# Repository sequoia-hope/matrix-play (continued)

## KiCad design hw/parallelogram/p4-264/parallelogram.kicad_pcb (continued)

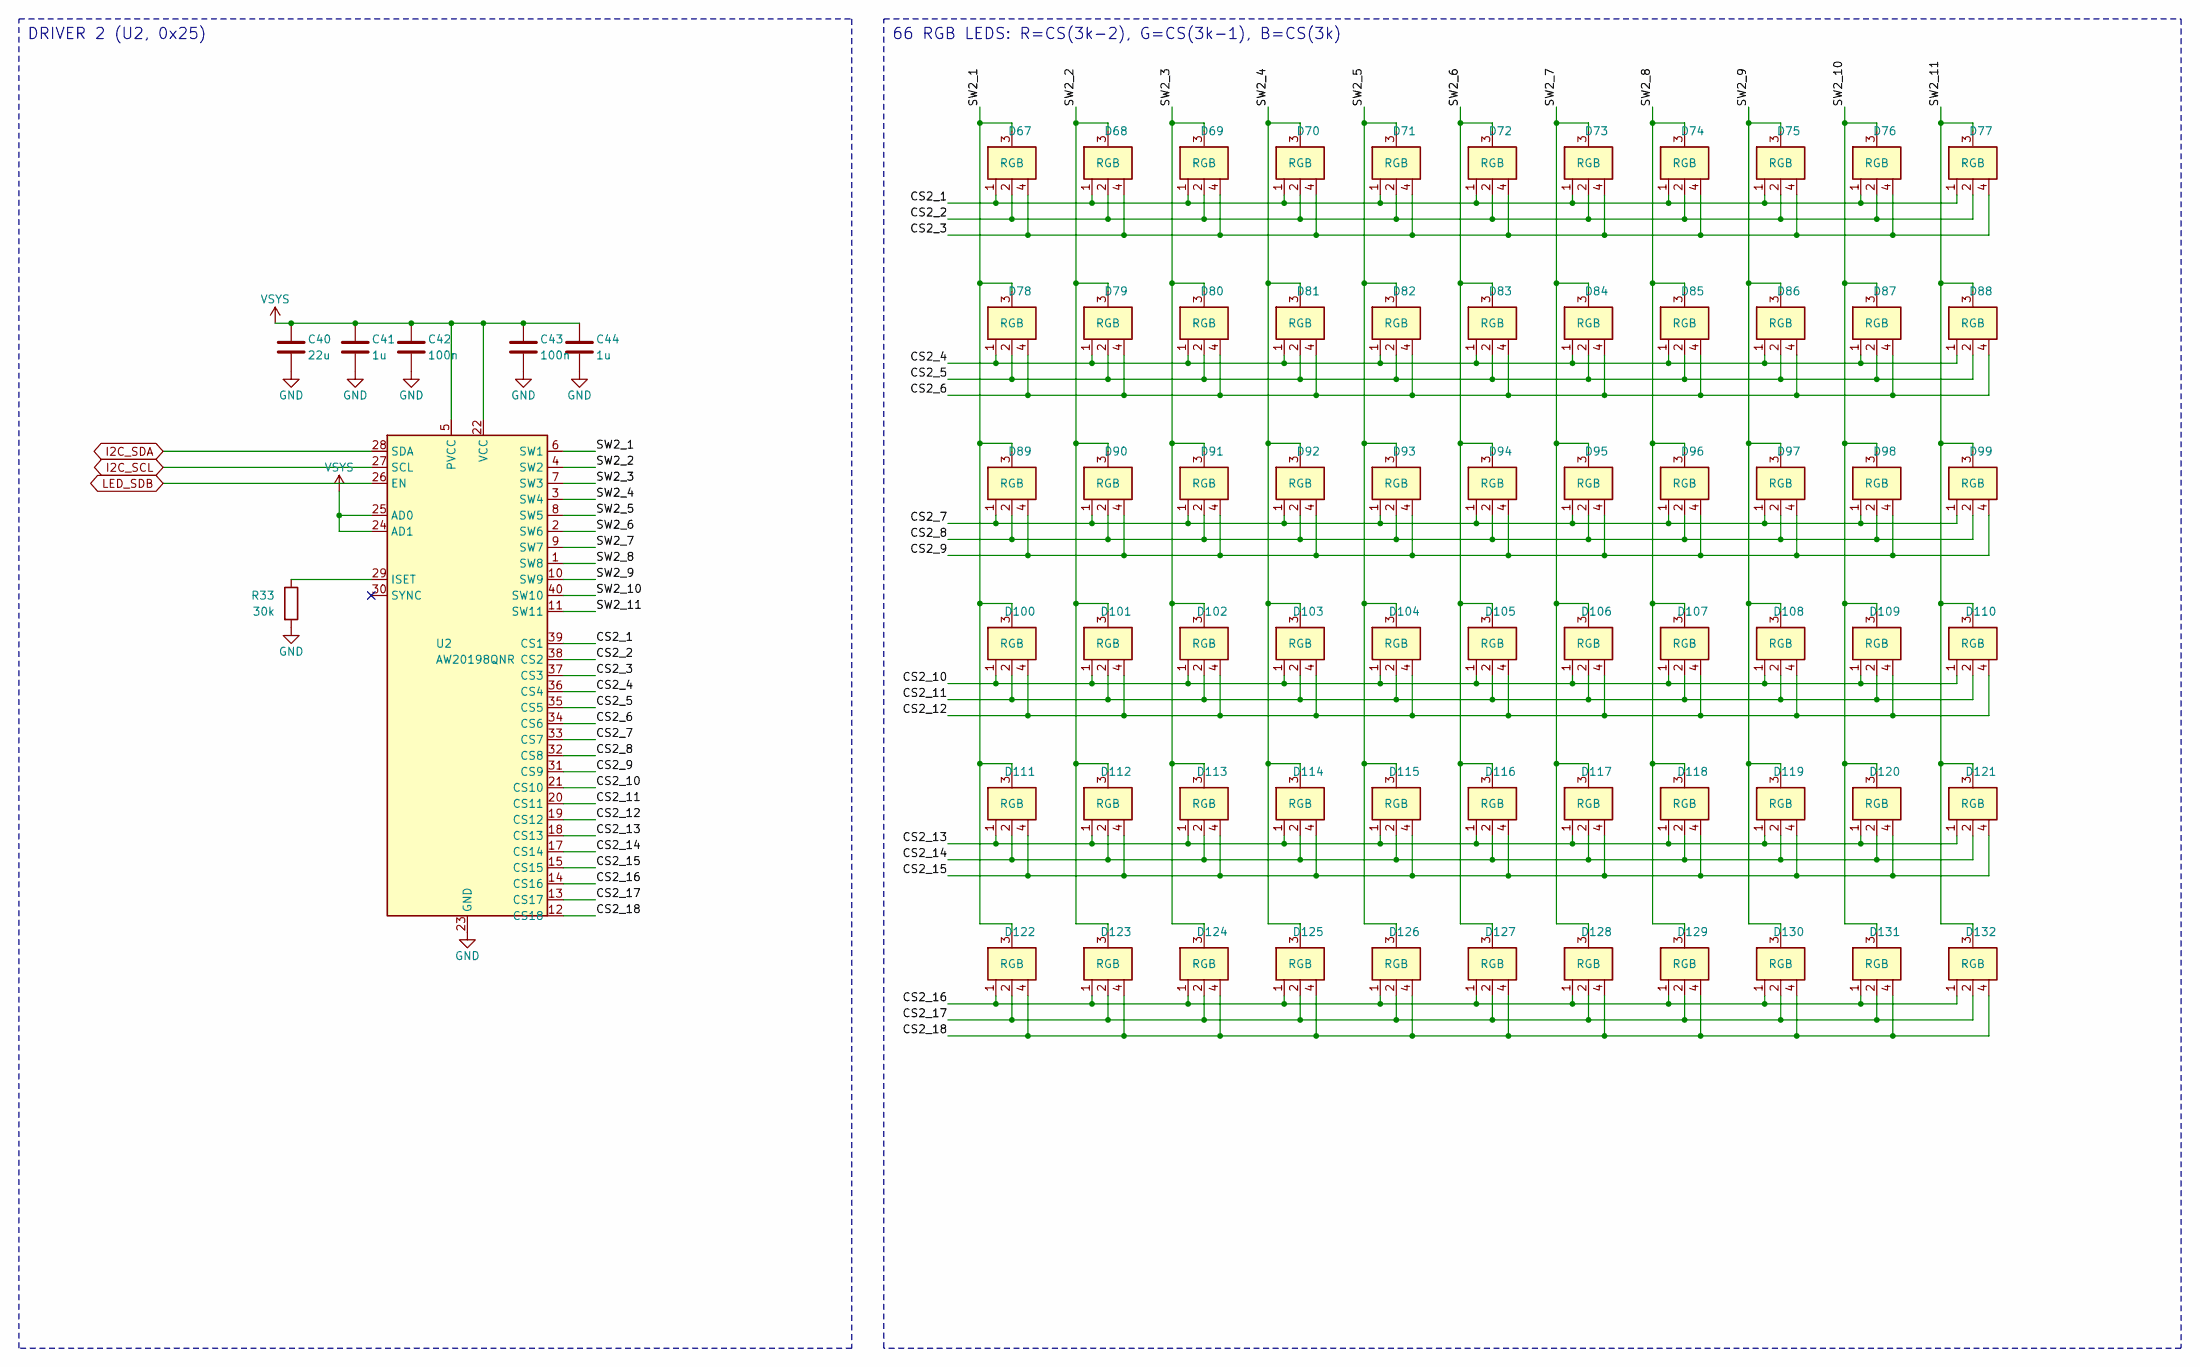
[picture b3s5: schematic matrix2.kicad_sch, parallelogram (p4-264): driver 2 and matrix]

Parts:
C40: 22u; C_0603_1608Metric; MPN CL10A226MP8NUNE; LCSC C86295
C41, C44: 1u; C_0402_1005Metric; MPN CL05A105KA5NQNC; LCSC C52923
C42, C43: 100n; C_0402_1005Metric; MPN CL05B104KO5NNNC; LCSC C1525
D67, D68, D69, D70, D71, D72, D73, D74, D75, D76, D77, D78, D79, D80, D81, D82, D83, D84, D85, D86, D87, D88, D89, D90, D91, D92, D93, D94, D95, D96, D97, D98, D99, D100, D101, D102, D103, D104, D105, D106, D107, D108, D109, D110, D111, D112, D113, D114, D115, D116, D117, D118, D119, D120, D121, D122, D123, D124, D125, D126, D127, D128, D129, D130, D131, D132: RGB; LED_XL-1010RGB; MPN XL-1010RGB-YG; LCSC C965834
R33: 30k; R_0402_1005Metric; MPN 0402WGF3002TCE; LCSC C25776
U2: AW20198QNR; AW20198_QFN-40-1EP_5x5mm_P0.4mm_EP3.4x3.4mm; MPN AW20198QNR; LCSC C5137654

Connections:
/Driver 2 and matrix/CS2_1: D67.1 (R), D68.1 (R), D69.1 (R), D70.1 (R), D71.1 (R), D72.1 (R), D73.1 (R), D74.1 (R), D75.1 (R), D76.1 (R), D77.1 (R), U2.39 (CS1)
/Driver 2 and matrix/CS2_2: D67.2 (G), D68.2 (G), D69.2 (G), D70.2 (G), D71.2 (G), D72.2 (G), D73.2 (G), D74.2 (G), D75.2 (G), D76.2 (G), D77.2 (G), U2.38 (CS2)
/Driver 2 and matrix/CS2_3: D67.4 (B), D68.4 (B), D69.4 (B), D70.4 (B), D71.4 (B), D72.4 (B), D73.4 (B), D74.4 (B), D75.4 (B), D76.4 (B), D77.4 (B), U2.37 (CS3)
/Driver 2 and matrix/CS2_4: D78.1 (R), D79.1 (R), D80.1 (R), D81.1 (R), D82.1 (R), D83.1 (R), D84.1 (R), D85.1 (R), D86.1 (R), D87.1 (R), D88.1 (R), U2.36 (CS4)
/Driver 2 and matrix/CS2_5: D78.2 (G), D79.2 (G), D80.2 (G), D81.2 (G), D82.2 (G), D83.2 (G), D84.2 (G), D85.2 (G), D86.2 (G), D87.2 (G), D88.2 (G), U2.35 (CS5)
/Driver 2 and matrix/CS2_6: D78.4 (B), D79.4 (B), D80.4 (B), D81.4 (B), D82.4 (B), D83.4 (B), D84.4 (B), D85.4 (B), D86.4 (B), D87.4 (B), D88.4 (B), U2.34 (CS6)
/Driver 2 and matrix/CS2_7: D89.1 (R), D90.1 (R), D91.1 (R), D92.1 (R), D93.1 (R), D94.1 (R), D95.1 (R), D96.1 (R), D97.1 (R), D98.1 (R), D99.1 (R), U2.33 (CS7)
/Driver 2 and matrix/CS2_8: D89.2 (G), D90.2 (G), D91.2 (G), D92.2 (G), D93.2 (G), D94.2 (G), D95.2 (G), D96.2 (G), D97.2 (G), D98.2 (G), D99.2 (G), U2.32 (CS8)
/Driver 2 and matrix/CS2_9: D89.4 (B), D90.4 (B), D91.4 (B), D92.4 (B), D93.4 (B), D94.4 (B), D95.4 (B), D96.4 (B), D97.4 (B), D98.4 (B), D99.4 (B), U2.31 (CS9)
/Driver 2 and matrix/CS2_10: D100.1 (R), D101.1 (R), D102.1 (R), D103.1 (R), D104.1 (R), D105.1 (R), D106.1 (R), D107.1 (R), D108.1 (R), D109.1 (R), D110.1 (R), U2.21 (CS10)
/Driver 2 and matrix/CS2_11: D100.2 (G), D101.2 (G), D102.2 (G), D103.2 (G), D104.2 (G), D105.2 (G), D106.2 (G), D107.2 (G), D108.2 (G), D109.2 (G), D110.2 (G), U2.20 (CS11)
/Driver 2 and matrix/CS2_12: D100.4 (B), D101.4 (B), D102.4 (B), D103.4 (B), D104.4 (B), D105.4 (B), D106.4 (B), D107.4 (B), D108.4 (B), D109.4 (B), D110.4 (B), U2.19 (CS12)
/Driver 2 and matrix/CS2_13: D111.1 (R), D112.1 (R), D113.1 (R), D114.1 (R), D115.1 (R), D116.1 (R), D117.1 (R), D118.1 (R), D119.1 (R), D120.1 (R), D121.1 (R), U2.18 (CS13)
/Driver 2 and matrix/CS2_14: D111.2 (G), D112.2 (G), D113.2 (G), D114.2 (G), D115.2 (G), D116.2 (G), D117.2 (G), D118.2 (G), D119.2 (G), D120.2 (G), D121.2 (G), U2.17 (CS14)
/Driver 2 and matrix/CS2_15: D111.4 (B), D112.4 (B), D113.4 (B), D114.4 (B), D115.4 (B), D116.4 (B), D117.4 (B), D118.4 (B), D119.4 (B), D120.4 (B), D121.4 (B), U2.15 (CS15)
/Driver 2 and matrix/CS2_16: D122.1 (R), D123.1 (R), D124.1 (R), D125.1 (R), D126.1 (R), D127.1 (R), D128.1 (R), D129.1 (R), D130.1 (R), D131.1 (R), D132.1 (R), U2.14 (CS16)
/Driver 2 and matrix/CS2_17: D122.2 (G), D123.2 (G), D124.2 (G), D125.2 (G), D126.2 (G), D127.2 (G), D128.2 (G), D129.2 (G), D130.2 (G), D131.2 (G), D132.2 (G), U2.13 (CS17)
/Driver 2 and matrix/CS2_18: D122.4 (B), D123.4 (B), D124.4 (B), D125.4 (B), D126.4 (B), D127.4 (B), D128.4 (B), D129.4 (B), D130.4 (B), D131.4 (B), D132.4 (B), U2.12 (CS18)
/Driver 2 and matrix/SW2_1: D67.3 (A), D78.3 (A), D89.3 (A), D100.3 (A), D111.3 (A), D122.3 (A), U2.6 (SW1)
/Driver 2 and matrix/SW2_2: D68.3 (A), D79.3 (A), D90.3 (A), D101.3 (A), D112.3 (A), D123.3 (A), U2.4 (SW2)
/Driver 2 and matrix/SW2_3: D69.3 (A), D80.3 (A), D91.3 (A), D102.3 (A), D113.3 (A), D124.3 (A), U2.7 (SW3)
/Driver 2 and matrix/SW2_4: D70.3 (A), D81.3 (A), D92.3 (A), D103.3 (A), D114.3 (A), D125.3 (A), U2.3 (SW4)
/Driver 2 and matrix/SW2_5: D71.3 (A), D82.3 (A), D93.3 (A), D104.3 (A), D115.3 (A), D126.3 (A), U2.8 (SW5)
/Driver 2 and matrix/SW2_6: D72.3 (A), D83.3 (A), D94.3 (A), D105.3 (A), D116.3 (A), D127.3 (A), U2.2 (SW6)
/Driver 2 and matrix/SW2_7: D73.3 (A), D84.3 (A), D95.3 (A), D106.3 (A), D117.3 (A), D128.3 (A), U2.9 (SW7)
/Driver 2 and matrix/SW2_8: D74.3 (A), D85.3 (A), D96.3 (A), D107.3 (A), D118.3 (A), D129.3 (A), U2.1 (SW8)
/Driver 2 and matrix/SW2_9: D75.3 (A), D86.3 (A), D97.3 (A), D108.3 (A), D119.3 (A), D130.3 (A), U2.10 (SW9)
/Driver 2 and matrix/SW2_10: D76.3 (A), D87.3 (A), D98.3 (A), D109.3 (A), D120.3 (A), D131.3 (A), U2.40 (SW10)
/Driver 2 and matrix/SW2_11: D77.3 (A), D88.3 (A), D99.3 (A), D110.3 (A), D121.3 (A), D132.3 (A), U2.11 (SW11)
I2C_SCL: U2.27 (SCL); also elsewhere on the board
I2C_SDA: U2.28 (SDA); also elsewhere on the board
LED_SDB: U2.26 (EN); also elsewhere on the board
unnamed: R33.1, U2.29 (ISET)
VSYS: C40.1, C41.1, C42.1, C43.1, C44.1, U2.5 (PVCC), U2.22 (VCC), U2.24 (AD1), U2.25 (AD0); also elsewhere on the board

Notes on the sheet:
DRIVER 2 (U2, 0x25)
66 RGB LEDS: R=CS(3k-2), G=CS(3k-1), B=CS(3k)

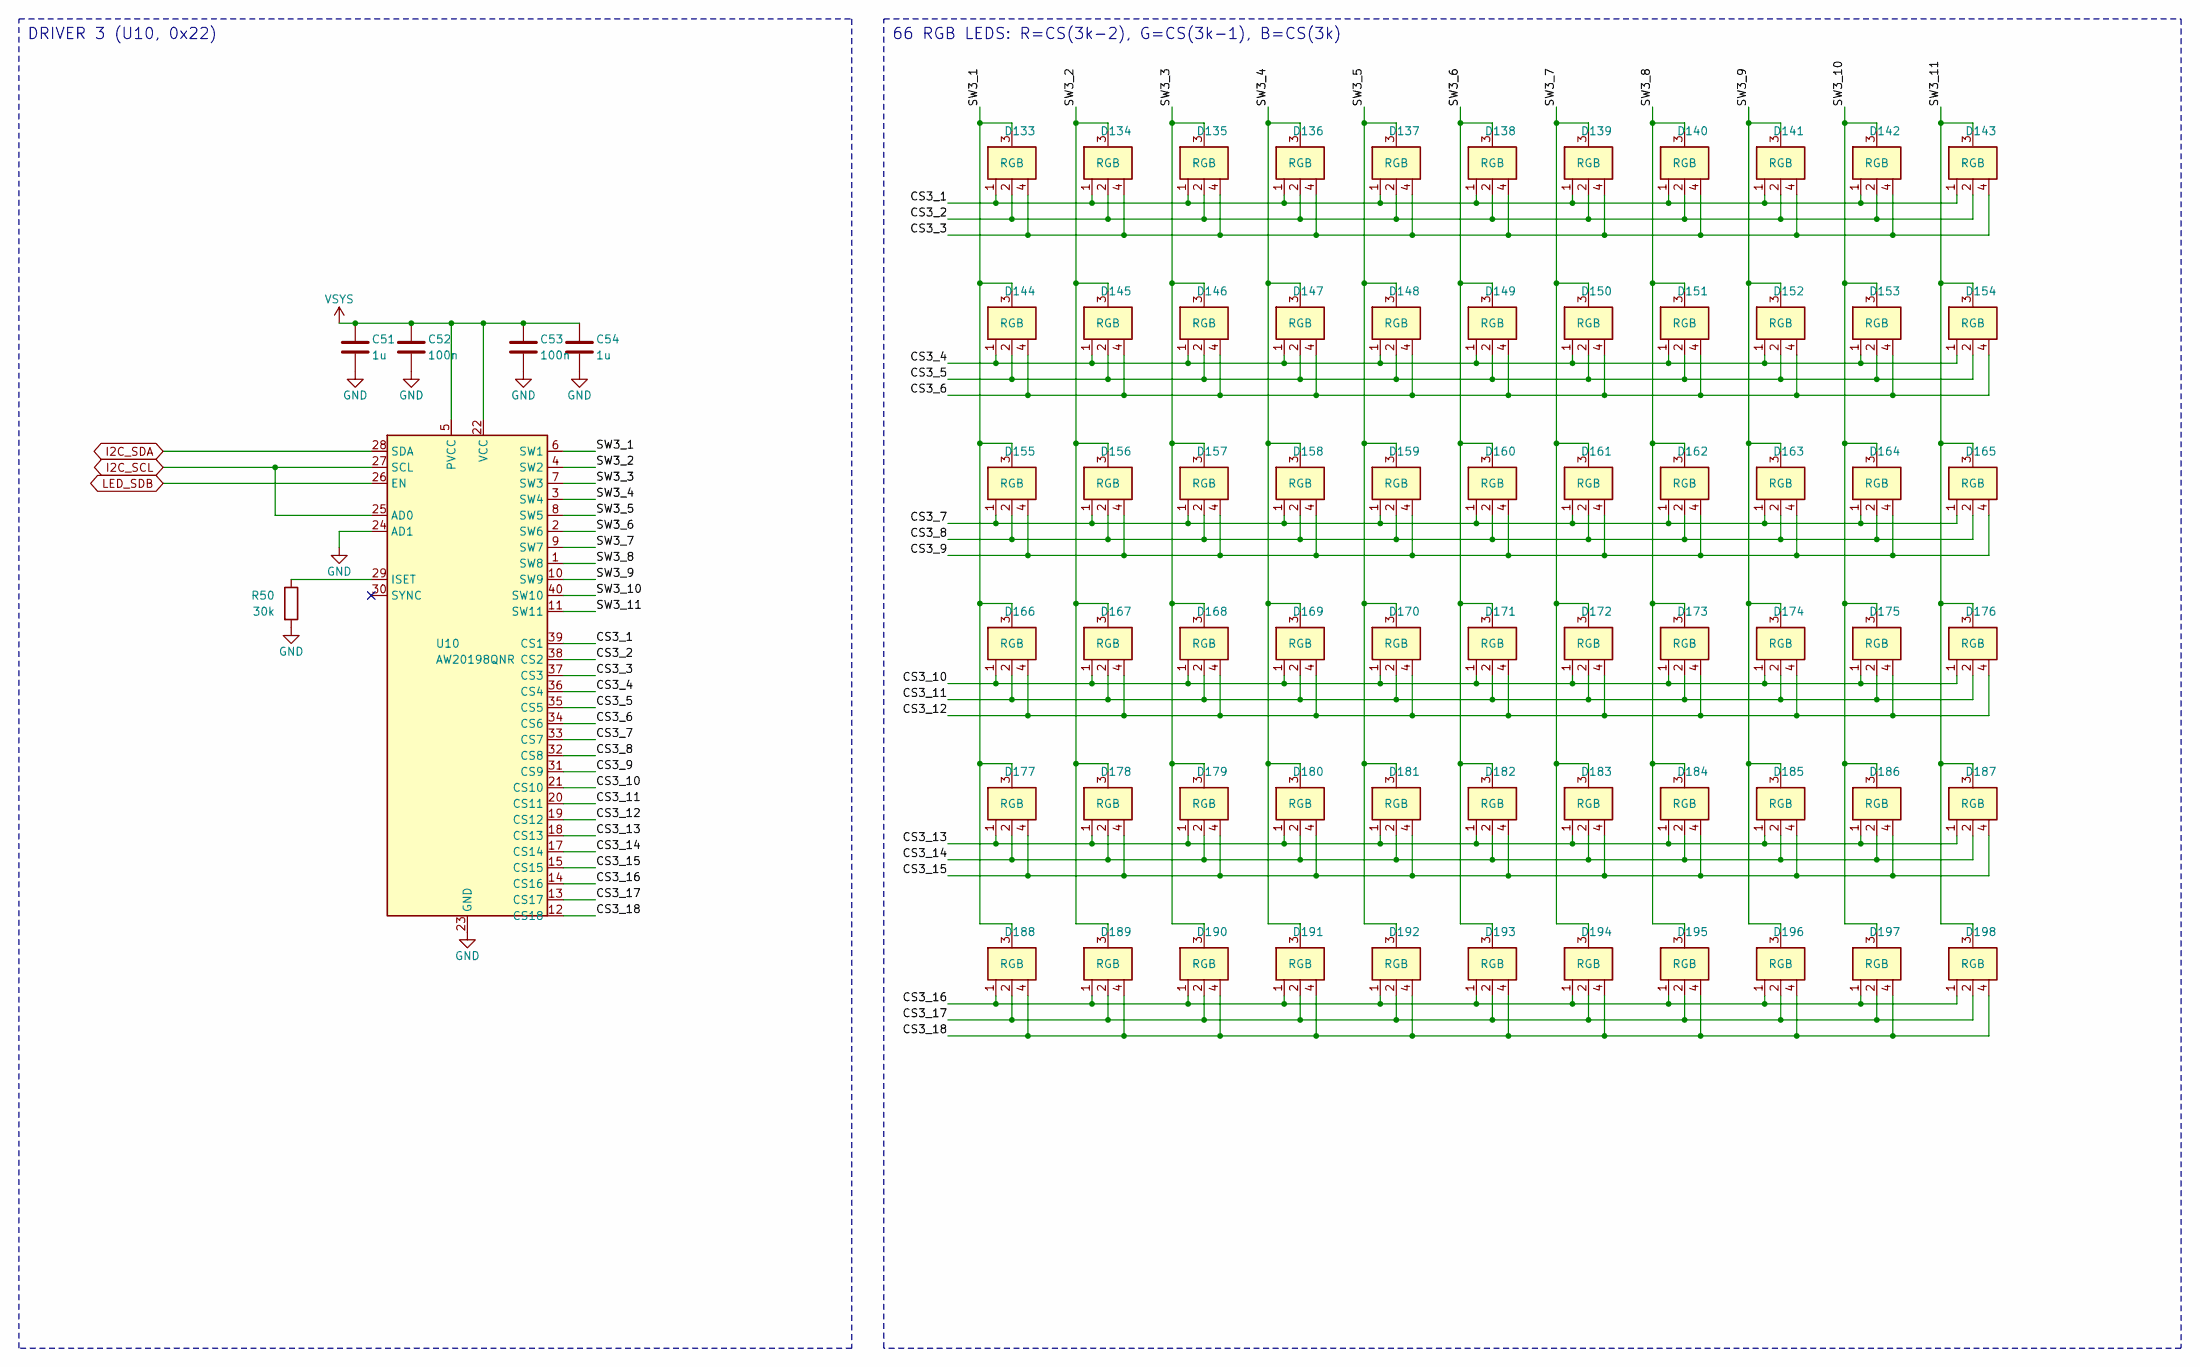
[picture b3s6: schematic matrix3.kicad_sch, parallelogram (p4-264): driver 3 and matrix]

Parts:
C51, C54: 1u; C_0402_1005Metric; MPN CL05A105KA5NQNC; LCSC C52923
C52, C53: 100n; C_0402_1005Metric; MPN CL05B104KO5NNNC; LCSC C1525
D133, D134, D135, D136, D137, D138, D139, D140, D141, D142, D143, D144, D145, D146, D147, D148, D149, D150, D151, D152, D153, D154, D155, D156, D157, D158, D159, D160, D161, D162, D163, D164, D165, D166, D167, D168, D169, D170, D171, D172, D173, D174, D175, D176, D177, D178, D179, D180, D181, D182, D183, D184, D185, D186, D187, D188, D189, D190, D191, D192, D193, D194, D195, D196, D197, D198: RGB; LED_XL-1010RGB; MPN XL-1010RGB-YG; LCSC C965834
R50: 30k; R_0402_1005Metric; MPN 0402WGF3002TCE; LCSC C25776
U10: AW20198QNR; AW20198_QFN-40-1EP_5x5mm_P0.4mm_EP3.4x3.4mm; MPN AW20198QNR; LCSC C5137654

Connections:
/Driver 3 and matrix/CS3_1: D133.1 (R), D134.1 (R), D135.1 (R), D136.1 (R), D137.1 (R), D138.1 (R), D139.1 (R), D140.1 (R), D141.1 (R), D142.1 (R), D143.1 (R), U10.39 (CS1)
/Driver 3 and matrix/CS3_2: D133.2 (G), D134.2 (G), D135.2 (G), D136.2 (G), D137.2 (G), D138.2 (G), D139.2 (G), D140.2 (G), D141.2 (G), D142.2 (G), D143.2 (G), U10.38 (CS2)
/Driver 3 and matrix/CS3_3: D133.4 (B), D134.4 (B), D135.4 (B), D136.4 (B), D137.4 (B), D138.4 (B), D139.4 (B), D140.4 (B), D141.4 (B), D142.4 (B), D143.4 (B), U10.37 (CS3)
/Driver 3 and matrix/CS3_4: D144.1 (R), D145.1 (R), D146.1 (R), D147.1 (R), D148.1 (R), D149.1 (R), D150.1 (R), D151.1 (R), D152.1 (R), D153.1 (R), D154.1 (R), U10.36 (CS4)
/Driver 3 and matrix/CS3_5: D144.2 (G), D145.2 (G), D146.2 (G), D147.2 (G), D148.2 (G), D149.2 (G), D150.2 (G), D151.2 (G), D152.2 (G), D153.2 (G), D154.2 (G), U10.35 (CS5)
/Driver 3 and matrix/CS3_6: D144.4 (B), D145.4 (B), D146.4 (B), D147.4 (B), D148.4 (B), D149.4 (B), D150.4 (B), D151.4 (B), D152.4 (B), D153.4 (B), D154.4 (B), U10.34 (CS6)
/Driver 3 and matrix/CS3_7: D155.1 (R), D156.1 (R), D157.1 (R), D158.1 (R), D159.1 (R), D160.1 (R), D161.1 (R), D162.1 (R), D163.1 (R), D164.1 (R), D165.1 (R), U10.33 (CS7)
/Driver 3 and matrix/CS3_8: D155.2 (G), D156.2 (G), D157.2 (G), D158.2 (G), D159.2 (G), D160.2 (G), D161.2 (G), D162.2 (G), D163.2 (G), D164.2 (G), D165.2 (G), U10.32 (CS8)
/Driver 3 and matrix/CS3_9: D155.4 (B), D156.4 (B), D157.4 (B), D158.4 (B), D159.4 (B), D160.4 (B), D161.4 (B), D162.4 (B), D163.4 (B), D164.4 (B), D165.4 (B), U10.31 (CS9)
/Driver 3 and matrix/CS3_10: D166.1 (R), D167.1 (R), D168.1 (R), D169.1 (R), D170.1 (R), D171.1 (R), D172.1 (R), D173.1 (R), D174.1 (R), D175.1 (R), D176.1 (R), U10.21 (CS10)
/Driver 3 and matrix/CS3_11: D166.2 (G), D167.2 (G), D168.2 (G), D169.2 (G), D170.2 (G), D171.2 (G), D172.2 (G), D173.2 (G), D174.2 (G), D175.2 (G), D176.2 (G), U10.20 (CS11)
/Driver 3 and matrix/CS3_12: D166.4 (B), D167.4 (B), D168.4 (B), D169.4 (B), D170.4 (B), D171.4 (B), D172.4 (B), D173.4 (B), D174.4 (B), D175.4 (B), D176.4 (B), U10.19 (CS12)
/Driver 3 and matrix/CS3_13: D177.1 (R), D178.1 (R), D179.1 (R), D180.1 (R), D181.1 (R), D182.1 (R), D183.1 (R), D184.1 (R), D185.1 (R), D186.1 (R), D187.1 (R), U10.18 (CS13)
/Driver 3 and matrix/CS3_14: D177.2 (G), D178.2 (G), D179.2 (G), D180.2 (G), D181.2 (G), D182.2 (G), D183.2 (G), D184.2 (G), D185.2 (G), D186.2 (G), D187.2 (G), U10.17 (CS14)
/Driver 3 and matrix/CS3_15: D177.4 (B), D178.4 (B), D179.4 (B), D180.4 (B), D181.4 (B), D182.4 (B), D183.4 (B), D184.4 (B), D185.4 (B), D186.4 (B), D187.4 (B), U10.15 (CS15)
/Driver 3 and matrix/CS3_16: D188.1 (R), D189.1 (R), D190.1 (R), D191.1 (R), D192.1 (R), D193.1 (R), D194.1 (R), D195.1 (R), D196.1 (R), D197.1 (R), D198.1 (R), U10.14 (CS16)
/Driver 3 and matrix/CS3_17: D188.2 (G), D189.2 (G), D190.2 (G), D191.2 (G), D192.2 (G), D193.2 (G), D194.2 (G), D195.2 (G), D196.2 (G), D197.2 (G), D198.2 (G), U10.13 (CS17)
/Driver 3 and matrix/CS3_18: D188.4 (B), D189.4 (B), D190.4 (B), D191.4 (B), D192.4 (B), D193.4 (B), D194.4 (B), D195.4 (B), D196.4 (B), D197.4 (B), D198.4 (B), U10.12 (CS18)
/Driver 3 and matrix/SW3_1: D133.3 (A), D144.3 (A), D155.3 (A), D166.3 (A), D177.3 (A), D188.3 (A), U10.6 (SW1)
/Driver 3 and matrix/SW3_2: D134.3 (A), D145.3 (A), D156.3 (A), D167.3 (A), D178.3 (A), D189.3 (A), U10.4 (SW2)
/Driver 3 and matrix/SW3_3: D135.3 (A), D146.3 (A), D157.3 (A), D168.3 (A), D179.3 (A), D190.3 (A), U10.7 (SW3)
/Driver 3 and matrix/SW3_4: D136.3 (A), D147.3 (A), D158.3 (A), D169.3 (A), D180.3 (A), D191.3 (A), U10.3 (SW4)
/Driver 3 and matrix/SW3_5: D137.3 (A), D148.3 (A), D159.3 (A), D170.3 (A), D181.3 (A), D192.3 (A), U10.8 (SW5)
/Driver 3 and matrix/SW3_6: D138.3 (A), D149.3 (A), D160.3 (A), D171.3 (A), D182.3 (A), D193.3 (A), U10.2 (SW6)
/Driver 3 and matrix/SW3_7: D139.3 (A), D150.3 (A), D161.3 (A), D172.3 (A), D183.3 (A), D194.3 (A), U10.9 (SW7)
/Driver 3 and matrix/SW3_8: D140.3 (A), D151.3 (A), D162.3 (A), D173.3 (A), D184.3 (A), D195.3 (A), U10.1 (SW8)
/Driver 3 and matrix/SW3_9: D141.3 (A), D152.3 (A), D163.3 (A), D174.3 (A), D185.3 (A), D196.3 (A), U10.10 (SW9)
/Driver 3 and matrix/SW3_10: D142.3 (A), D153.3 (A), D164.3 (A), D175.3 (A), D186.3 (A), D197.3 (A), U10.40 (SW10)
/Driver 3 and matrix/SW3_11: D143.3 (A), D154.3 (A), D165.3 (A), D176.3 (A), D187.3 (A), D198.3 (A), U10.11 (SW11)
I2C_SCL: U10.25 (AD0), U10.27 (SCL); also elsewhere on the board
I2C_SDA: U10.28 (SDA); also elsewhere on the board
LED_SDB: U10.26 (EN); also elsewhere on the board
unnamed: R50.1, U10.29 (ISET)
VSYS: C51.1, C52.1, C53.1, C54.1, U10.5 (PVCC), U10.22 (VCC); also elsewhere on the board

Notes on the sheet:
DRIVER 3 (U10, 0x22)
66 RGB LEDS: R=CS(3k-2), G=CS(3k-1), B=CS(3k)

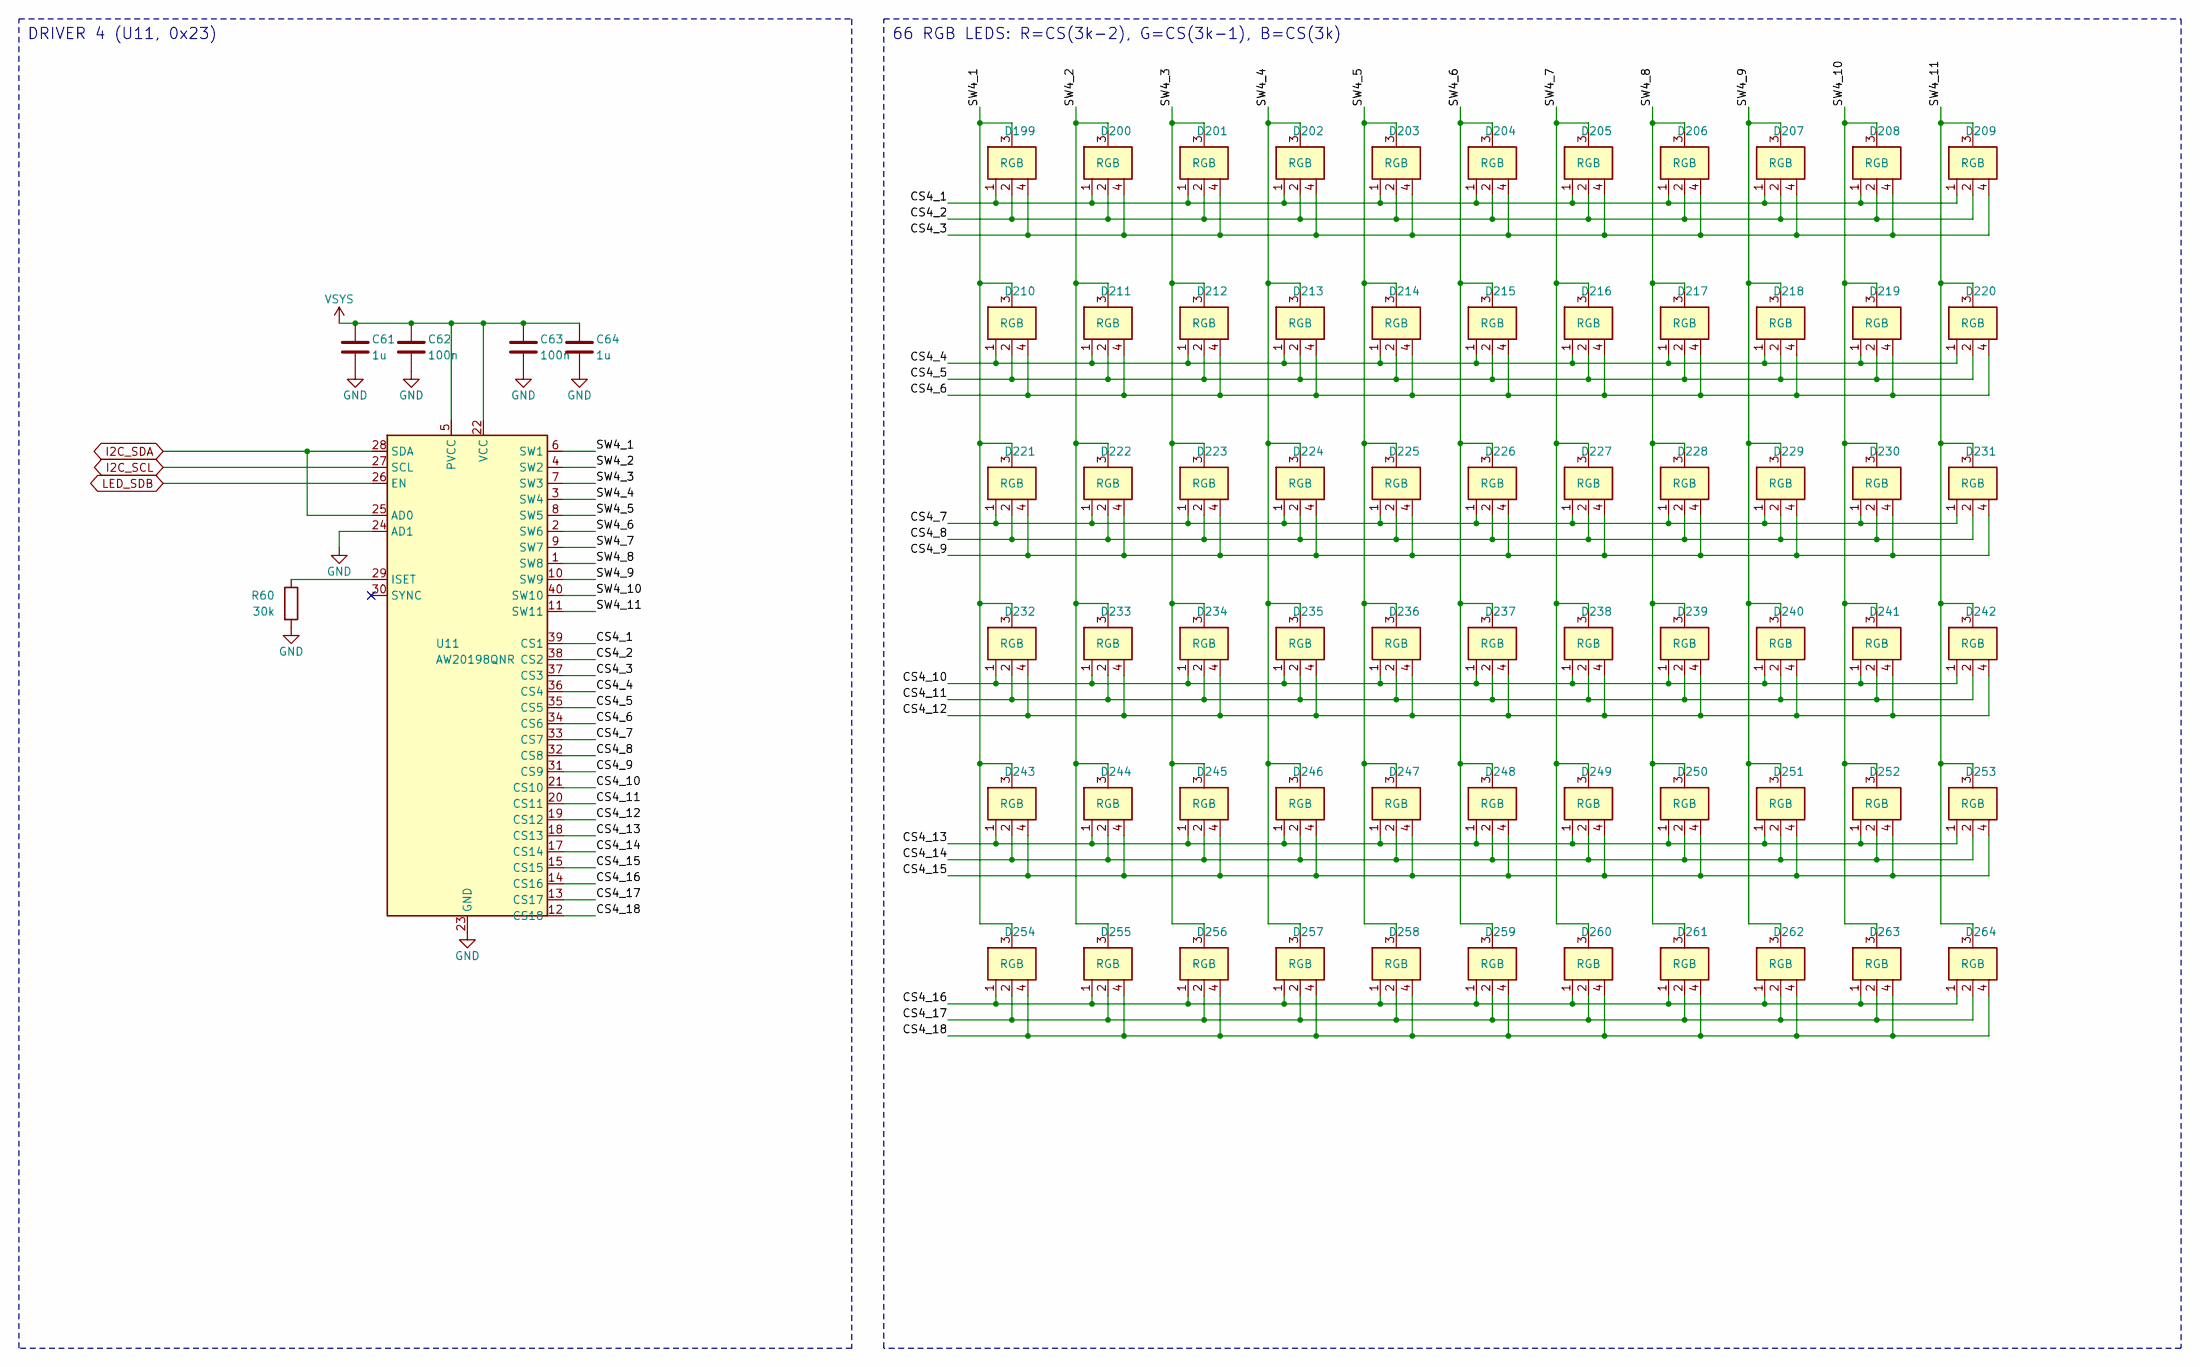
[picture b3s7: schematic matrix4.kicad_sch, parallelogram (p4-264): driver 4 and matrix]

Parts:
C61, C64: 1u; C_0402_1005Metric; MPN CL05A105KA5NQNC; LCSC C52923
C62, C63: 100n; C_0402_1005Metric; MPN CL05B104KO5NNNC; LCSC C1525
D199, D200, D201, D202, D203, D204, D205, D206, D207, D208, D209, D210, D211, D212, D213, D214, D215, D216, D217, D218, D219, D220, D221, D222, D223, D224, D225, D226, D227, D228, D229, D230, D231, D232, D233, D234, D235, D236, D237, D238, D239, D240, D241, D242, D243, D244, D245, D246, D247, D248, D249, D250, D251, D252, D253, D254, D255, D256, D257, D258, D259, D260, D261, D262, D263, D264: RGB; LED_XL-1010RGB; MPN XL-1010RGB-YG; LCSC C965834
R60: 30k; R_0402_1005Metric; MPN 0402WGF3002TCE; LCSC C25776
U11: AW20198QNR; AW20198_QFN-40-1EP_5x5mm_P0.4mm_EP3.4x3.4mm; MPN AW20198QNR; LCSC C5137654

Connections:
/Driver 4 and matrix/CS4_1: D199.1 (R), D200.1 (R), D201.1 (R), D202.1 (R), D203.1 (R), D204.1 (R), D205.1 (R), D206.1 (R), D207.1 (R), D208.1 (R), D209.1 (R), U11.39 (CS1)
/Driver 4 and matrix/CS4_2: D199.2 (G), D200.2 (G), D201.2 (G), D202.2 (G), D203.2 (G), D204.2 (G), D205.2 (G), D206.2 (G), D207.2 (G), D208.2 (G), D209.2 (G), U11.38 (CS2)
/Driver 4 and matrix/CS4_3: D199.4 (B), D200.4 (B), D201.4 (B), D202.4 (B), D203.4 (B), D204.4 (B), D205.4 (B), D206.4 (B), D207.4 (B), D208.4 (B), D209.4 (B), U11.37 (CS3)
/Driver 4 and matrix/CS4_4: D210.1 (R), D211.1 (R), D212.1 (R), D213.1 (R), D214.1 (R), D215.1 (R), D216.1 (R), D217.1 (R), D218.1 (R), D219.1 (R), D220.1 (R), U11.36 (CS4)
/Driver 4 and matrix/CS4_5: D210.2 (G), D211.2 (G), D212.2 (G), D213.2 (G), D214.2 (G), D215.2 (G), D216.2 (G), D217.2 (G), D218.2 (G), D219.2 (G), D220.2 (G), U11.35 (CS5)
/Driver 4 and matrix/CS4_6: D210.4 (B), D211.4 (B), D212.4 (B), D213.4 (B), D214.4 (B), D215.4 (B), D216.4 (B), D217.4 (B), D218.4 (B), D219.4 (B), D220.4 (B), U11.34 (CS6)
/Driver 4 and matrix/CS4_7: D221.1 (R), D222.1 (R), D223.1 (R), D224.1 (R), D225.1 (R), D226.1 (R), D227.1 (R), D228.1 (R), D229.1 (R), D230.1 (R), D231.1 (R), U11.33 (CS7)
/Driver 4 and matrix/CS4_8: D221.2 (G), D222.2 (G), D223.2 (G), D224.2 (G), D225.2 (G), D226.2 (G), D227.2 (G), D228.2 (G), D229.2 (G), D230.2 (G), D231.2 (G), U11.32 (CS8)
/Driver 4 and matrix/CS4_9: D221.4 (B), D222.4 (B), D223.4 (B), D224.4 (B), D225.4 (B), D226.4 (B), D227.4 (B), D228.4 (B), D229.4 (B), D230.4 (B), D231.4 (B), U11.31 (CS9)
/Driver 4 and matrix/CS4_10: D232.1 (R), D233.1 (R), D234.1 (R), D235.1 (R), D236.1 (R), D237.1 (R), D238.1 (R), D239.1 (R), D240.1 (R), D241.1 (R), D242.1 (R), U11.21 (CS10)
/Driver 4 and matrix/CS4_11: D232.2 (G), D233.2 (G), D234.2 (G), D235.2 (G), D236.2 (G), D237.2 (G), D238.2 (G), D239.2 (G), D240.2 (G), D241.2 (G), D242.2 (G), U11.20 (CS11)
/Driver 4 and matrix/CS4_12: D232.4 (B), D233.4 (B), D234.4 (B), D235.4 (B), D236.4 (B), D237.4 (B), D238.4 (B), D239.4 (B), D240.4 (B), D241.4 (B), D242.4 (B), U11.19 (CS12)
/Driver 4 and matrix/CS4_13: D243.1 (R), D244.1 (R), D245.1 (R), D246.1 (R), D247.1 (R), D248.1 (R), D249.1 (R), D250.1 (R), D251.1 (R), D252.1 (R), D253.1 (R), U11.18 (CS13)
/Driver 4 and matrix/CS4_14: D243.2 (G), D244.2 (G), D245.2 (G), D246.2 (G), D247.2 (G), D248.2 (G), D249.2 (G), D250.2 (G), D251.2 (G), D252.2 (G), D253.2 (G), U11.17 (CS14)
/Driver 4 and matrix/CS4_15: D243.4 (B), D244.4 (B), D245.4 (B), D246.4 (B), D247.4 (B), D248.4 (B), D249.4 (B), D250.4 (B), D251.4 (B), D252.4 (B), D253.4 (B), U11.15 (CS15)
/Driver 4 and matrix/CS4_16: D254.1 (R), D255.1 (R), D256.1 (R), D257.1 (R), D258.1 (R), D259.1 (R), D260.1 (R), D261.1 (R), D262.1 (R), D263.1 (R), D264.1 (R), U11.14 (CS16)
/Driver 4 and matrix/CS4_17: D254.2 (G), D255.2 (G), D256.2 (G), D257.2 (G), D258.2 (G), D259.2 (G), D260.2 (G), D261.2 (G), D262.2 (G), D263.2 (G), D264.2 (G), U11.13 (CS17)
/Driver 4 and matrix/CS4_18: D254.4 (B), D255.4 (B), D256.4 (B), D257.4 (B), D258.4 (B), D259.4 (B), D260.4 (B), D261.4 (B), D262.4 (B), D263.4 (B), D264.4 (B), U11.12 (CS18)
/Driver 4 and matrix/SW4_1: D199.3 (A), D210.3 (A), D221.3 (A), D232.3 (A), D243.3 (A), D254.3 (A), U11.6 (SW1)
/Driver 4 and matrix/SW4_2: D200.3 (A), D211.3 (A), D222.3 (A), D233.3 (A), D244.3 (A), D255.3 (A), U11.4 (SW2)
/Driver 4 and matrix/SW4_3: D201.3 (A), D212.3 (A), D223.3 (A), D234.3 (A), D245.3 (A), D256.3 (A), U11.7 (SW3)
/Driver 4 and matrix/SW4_4: D202.3 (A), D213.3 (A), D224.3 (A), D235.3 (A), D246.3 (A), D257.3 (A), U11.3 (SW4)
/Driver 4 and matrix/SW4_5: D203.3 (A), D214.3 (A), D225.3 (A), D236.3 (A), D247.3 (A), D258.3 (A), U11.8 (SW5)
/Driver 4 and matrix/SW4_6: D204.3 (A), D215.3 (A), D226.3 (A), D237.3 (A), D248.3 (A), D259.3 (A), U11.2 (SW6)
/Driver 4 and matrix/SW4_7: D205.3 (A), D216.3 (A), D227.3 (A), D238.3 (A), D249.3 (A), D260.3 (A), U11.9 (SW7)
/Driver 4 and matrix/SW4_8: D206.3 (A), D217.3 (A), D228.3 (A), D239.3 (A), D250.3 (A), D261.3 (A), U11.1 (SW8)
/Driver 4 and matrix/SW4_9: D207.3 (A), D218.3 (A), D229.3 (A), D240.3 (A), D251.3 (A), D262.3 (A), U11.10 (SW9)
/Driver 4 and matrix/SW4_10: D208.3 (A), D219.3 (A), D230.3 (A), D241.3 (A), D252.3 (A), D263.3 (A), U11.40 (SW10)
/Driver 4 and matrix/SW4_11: D209.3 (A), D220.3 (A), D231.3 (A), D242.3 (A), D253.3 (A), D264.3 (A), U11.11 (SW11)
I2C_SCL: U11.27 (SCL); also elsewhere on the board
I2C_SDA: U11.25 (AD0), U11.28 (SDA); also elsewhere on the board
LED_SDB: U11.26 (EN); also elsewhere on the board
unnamed: R60.1, U11.29 (ISET)
VSYS: C61.1, C62.1, C63.1, C64.1, U11.5 (PVCC), U11.22 (VCC); also elsewhere on the board

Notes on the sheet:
DRIVER 4 (U11, 0x23)
66 RGB LEDS: R=CS(3k-2), G=CS(3k-1), B=CS(3k)

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
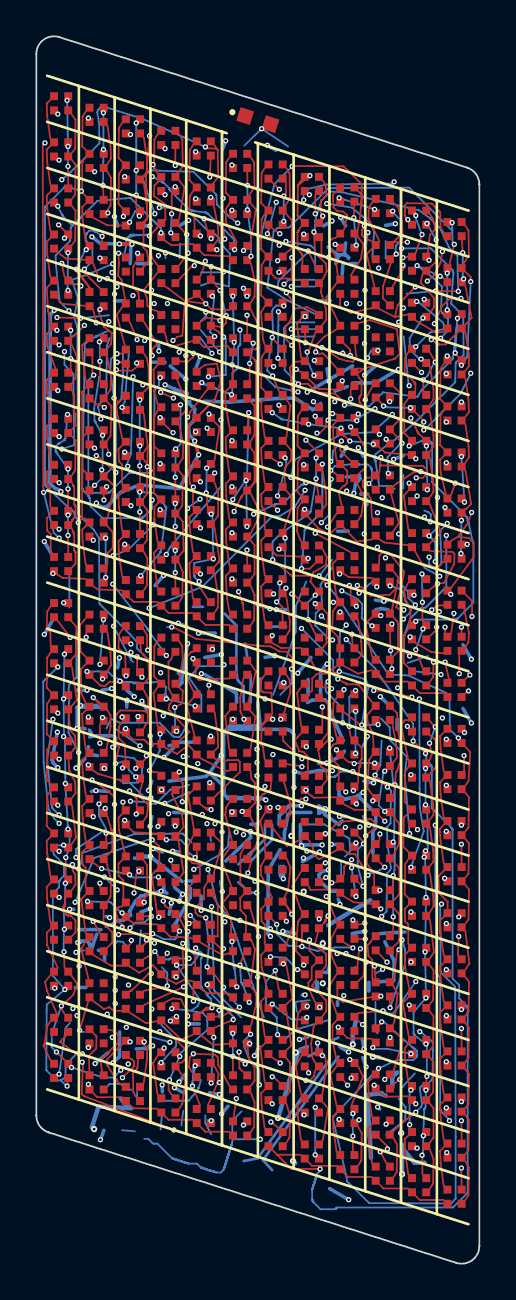
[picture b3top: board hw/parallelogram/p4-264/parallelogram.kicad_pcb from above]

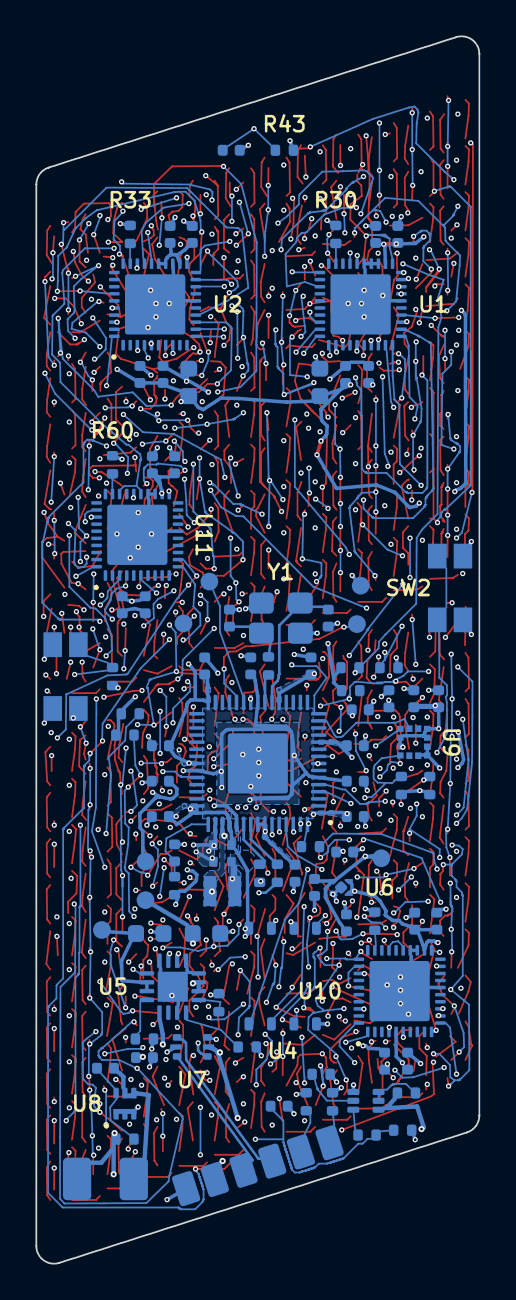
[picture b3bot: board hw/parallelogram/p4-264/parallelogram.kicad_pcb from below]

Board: 4 copper layers, 25.0 x 69.3 mm, 365 parts (100 on the bottom side), 170 nets.
